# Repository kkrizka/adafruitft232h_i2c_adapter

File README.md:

# Introduction
The [FT232H](http://www.ftdichip.com/Products/ICs/FT232H.htm) is a funky little chip that converts from USB to random serial protocols. It is useful for talking to devices that communicate via I2C or SPI. Adafruit has developed a [FT232H break-out board](https://learn.adafruit.com/adafruit-ft232h-breakout/) that connects to a computer using a micro-USB port. However to use it with I2C, some external electronics are required.
 
The Adafruit FT232H I2C Adapter is a custom PCB that connects to the break-out board and adds
* fuses the FT232H input pin with the output pin for the bi-directional SDA line,
* contains an LDO to generate the reference voltage from the USB power,
* pull-up resistors to the reference voltage.

The reference voltage can be set by picking the right resistor values, allowing for a wide operational range.

# Components

* **U1**: 2x [0.1" 1x10 pin sockets](https://www.digikey.com/products/en?keywords=s7043-ND) to connect the the Adafruit FT232H break-out board
* **U2**: [ADP123 LDO](https://www.digikey.com/products/en?keywords=12T2968), TSOT-5 package
* **C1-2**: Bypass capacitors, 1 uF
* **R1-R2**: Pull-up resistors, 2 kOhm
* **R3-R4**: Output of U2 LDO set I2C reference voltage. `Vout = 0.5V (1 + R3/R4)`.
* **J1**: Connectors to the I2C device. 4 0.1" 1x4 pin header recommended.

# FT232H Open Drain Pins
By default, the FT232H device is configured in the `RS232` mode. In thise mode, the D0, D1 and D2 pins (used for I2C communication) are driven internally at 3.3V. To take advantage of the external variable reference mode, they need to be put into open-drain mode. The Adafruit board contains an EEPROM that that configures the device on power-up. It has to be configured using the [FT_PROG](http://www.ftdichip.com/Support/Utilities.htm#FT_PROG) (Windows only) tool.

To use open-drain for the I2C pins, set the mode as `245 FIFO`. This setting can be found under
```
Device
 -> FT EEPROM
   -> Hardware Specific
     -> 245 FIFO
```

# Device Permissions
The device permissions need to be loosened to allow usage of the libftdi driver as a non-root user. The following udev rule allow any user in the `plugdev` group to access the FTDI232H device. 

```
SUBSYSTEMS=="usb", ATTRS{idVendor}=="0403", ATTRS{idProduct}=="6014", MODE:="0666", GROUP:="plugdev"
```

Add it to a file called `/etc/udev/rules.d/83-ftdi.rules` and run the following command to load it:
```shell
udevadm control --reload-rules && udevadm trigger
```

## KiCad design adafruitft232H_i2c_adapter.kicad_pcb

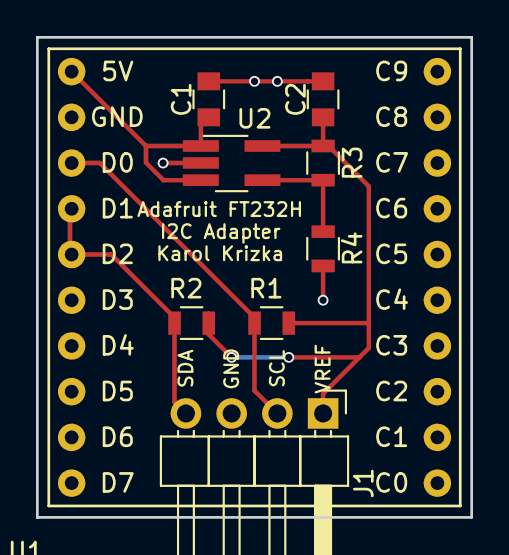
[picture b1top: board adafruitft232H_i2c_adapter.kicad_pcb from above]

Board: 2 copper layers, 24.1 x 26.7 mm, 9 parts (0 on the bottom side), 6 nets.

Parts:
C1, C2: 1uF; C_0805
J1: CONN_01X04; Pin_Header_Angled_1x04_Pitch2.54mm
R1, R2, R3, R4: R; R_0805
U1: adafruit_ft232h; adafruit_ft232h_nohole
U2: APD123; TSOT-23-5_HandSoldering

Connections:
/5V: C1.1, U1.1, U2.1, U2.3
/SCL: J1.2, R1.2, U1.3
/SDA: J1.4, R2.2, U1.4, U1.5
/VREF: C2.1, J1.1, R1.1, R2.1, R3.1, U2.5
GND: C1.2, C2.2, J1.3, R4.2, U1.2, U2.2
unnamed: R3.2, R4.1, U2.4

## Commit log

2018-01-04 Import empty project.
2018-01-04 Schematic done.
2018-01-04 Add fp-lib-table?
2018-01-05 Small layout updates to make silkscreen prettier. Add gerbers.
2018-01-05 Remove extra wires.
2018-01-05 Add name and title.
2018-04-03 Update the components list in the README.md.
2018-05-17 Update README with udev rule.
